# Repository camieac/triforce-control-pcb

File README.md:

# triforce-control-pcb

## Repository Navigation
This repository hosts the electronics hardware designs for the Triforce Fight Controller. Links to the main software repositories are below:

### [Triforce Control](https://github.com/TeamTriforceUK/triforce-control)

The Triforce Control firmware (mbed OS) runs on an LPC1768 (ARM Cortex M3). The firmware is responsible for controlling the robot.

### [Triforce Telemetry](https://github.com/TeamTriforceUK/triforce-telemetry)

The Triforce Telemetry repository hosts firmware (FreeRTOS) for the ESP8266 WiFi chip. This microcontroller works alongside the mbed to provide telemetry functionality via an HTTP server.

The ESP8266 allows us to communicate telemetry from Triforce to connected mobile devices (tablets, laptops, mobile phones). We also control non-safety critical settings such as LED lights from the mobile device.

## System Overview

### Microprocessors

| Device  | Firmware  | Language |
|---------|-----------|----------|
| [LPC1768](https://developer.mbed.org/platforms/mbed-LPC1768/) | [mbed OS](https://www.mbed.com/en/development/mbed-os/)   | C++      |
| [ESP8266](https://www.adafruit.com/product/2471) | [FreeRTOS](http://www.freertos.org/)  | C        |

### Sensors

| Sensor | Purpose                              | Communication |
|--------|--------------------------------------|---------------|
| [BNO055](https://learn.adafruit.com/adafruit-bno055-absolute-orientation-sensor/overview) | Orientation, direction, acceleration |  I2C          |

# PCB Spec

# Board Dimensions

| Width | Height | Thickness |
|-------|--------|-----------|
| 75mm  | 85mm   | 1.6mm     |

# Useful Links

## Enclosure

https://www.hammfg.com/files/parts/pdf/1455J1202.pdf
https://www.hammfg.com/part/1455J1202

## Generating gerber files

http://support.seeedstudio.com/knowledgebase/articles/1824574-how-to-generate-gerber-and-drill-files-from-kicad

## Contributing

We are open to any contributions in terms of ideas, suggestions, bug reports, development. Feel free to open GitHub issues regarding any contributions.

## Licensing

Licensed under CERN OHL v.1.2.

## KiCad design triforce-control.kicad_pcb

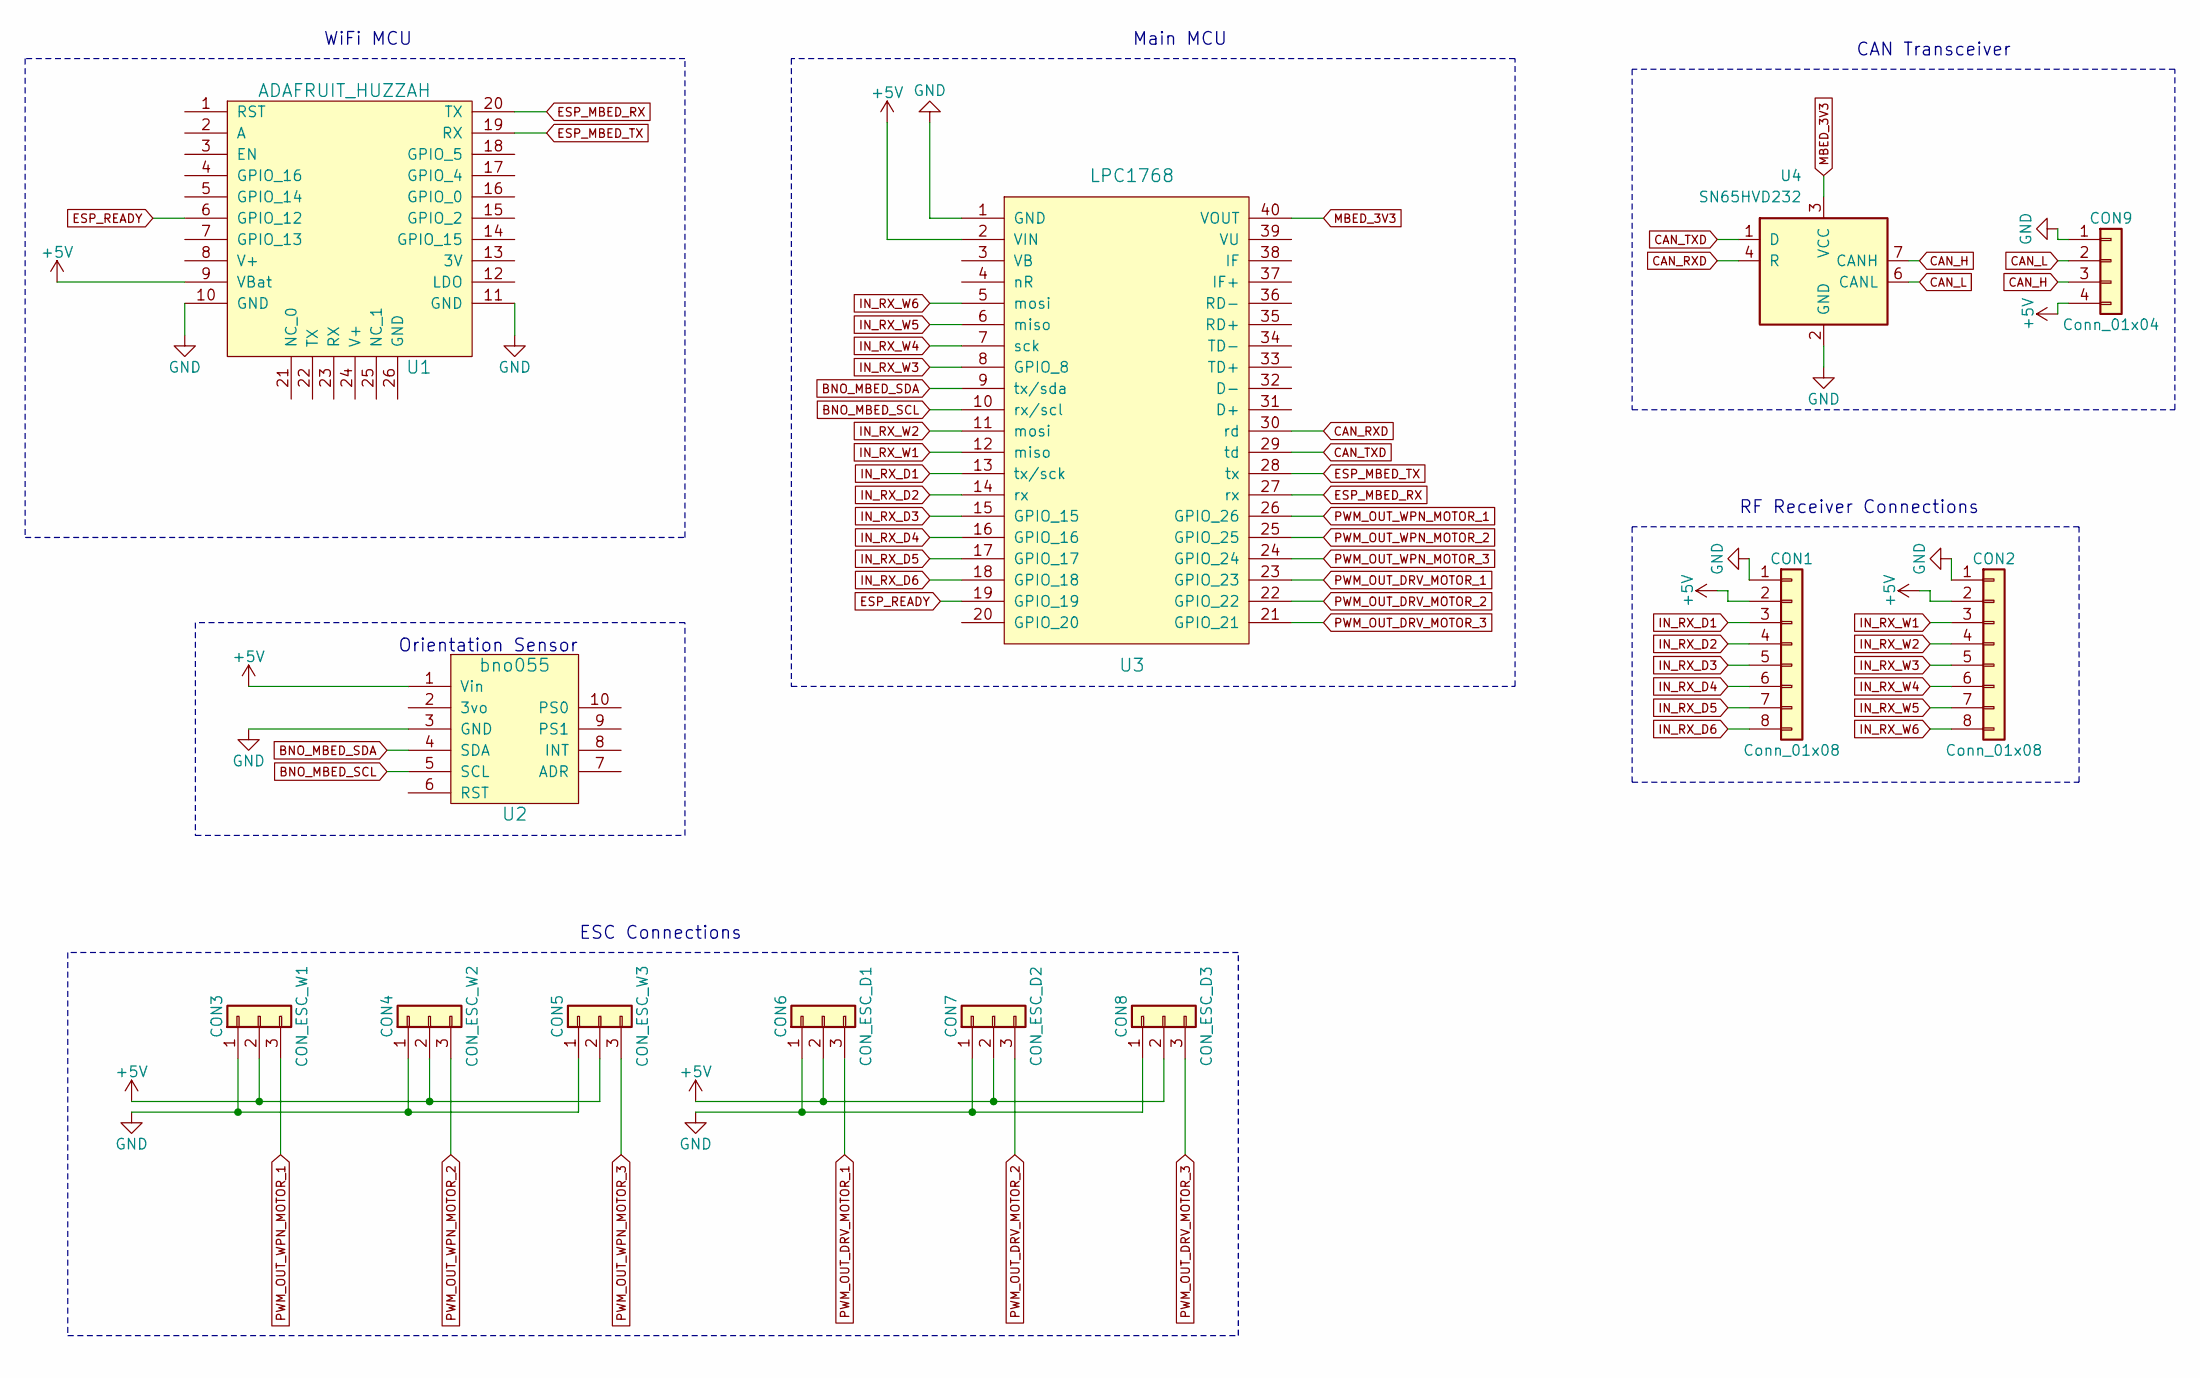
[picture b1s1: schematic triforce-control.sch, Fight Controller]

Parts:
CON1, CON2: Conn_01x08; JST_SH_SM08B-SRSS-TB_08x1.00mm_Angled
CON3: CON_ESC_W1; Pin_Header_Angled_3x01_Pitch2.54mm
CON4: CON_ESC_W2; Pin_Header_Angled_3x01_Pitch2.54mm
CON5: CON_ESC_W3; Pin_Header_Angled_3x01_Pitch2.54mm
CON6: CON_ESC_D1; Pin_Header_Angled_3x01_Pitch2.54mm
CON7: CON_ESC_D2; Pin_Header_Angled_3x01_Pitch2.54mm
CON8: CON_ESC_D3; Pin_Header_Angled_3x01_Pitch2.54mm
CON9: Conn_01x04; JST_PH_S4B-PH-K_04x2.00mm_Angled
U1: ADAFRUIT_HUZZAH; ESP8266
U2: bno055; BNO055
U3: LPC1768; lpc1768
U4: SN65HVD232; SOIC-8_3.9x4.9mm_Pitch1.27mm

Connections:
+5V: CON1.2, CON2.2, CON3.2, CON4.2, CON5.2, CON6.2, CON7.2, CON8.2, CON9.4, U1.9 (VBat), U2.1 (Vin), U3.2 (VIN); also elsewhere on the board
BNO_MBED_SCL: U2.5 (SCL), U3.10 (rx/scl); also elsewhere on the board
BNO_MBED_SDA: U2.4 (SDA), U3.9 (tx/sda); also elsewhere on the board
CAN_H: CON9.3, U4.7 (CANH)
CAN_L: CON9.2, U4.6 (CANL)
CAN_RXD: U3.30 (rd), U4.4 (R); also elsewhere on the board
CAN_TXD: U3.29 (td), U4.1 (D); also elsewhere on the board
ESP_MBED_RX: U1.20 (TX), U3.27 (rx); also elsewhere on the board
ESP_MBED_TX: U1.19 (RX), U3.28 (tx); also elsewhere on the board
ESP_READY: U1.6 (GPIO_12), U3.19 (GPIO_19); also elsewhere on the board
GND: CON1.1, CON2.1, CON3.1, CON4.1, CON5.1, CON6.1, CON7.1, CON8.1, CON9.1, U1.10 (GND), U1.11 (GND), U2.3 (GND), U3.1 (GND), U4.2 (GND); also elsewhere on the board
IN_RX_D1: CON1.3, U3.13 (tx/sck); also elsewhere on the board
IN_RX_D2: CON1.4, U3.14 (rx); also elsewhere on the board
IN_RX_D3: CON1.5, U3.15 (GPIO_15); also elsewhere on the board
IN_RX_D4: CON1.6, U3.16 (GPIO_16); also elsewhere on the board
IN_RX_D5: CON1.7, U3.17 (GPIO_17); also elsewhere on the board
IN_RX_D6: CON1.8, U3.18 (GPIO_18); also elsewhere on the board
IN_RX_W1: CON2.3, U3.12 (miso); also elsewhere on the board
IN_RX_W2: CON2.4, U3.11 (mosi); also elsewhere on the board
IN_RX_W3: CON2.5, U3.8 (GPIO_8); also elsewhere on the board
IN_RX_W4: CON2.6, U3.7 (sck); also elsewhere on the board
IN_RX_W5: CON2.7, U3.6 (miso); also elsewhere on the board
IN_RX_W6: CON2.8, U3.5 (mosi); also elsewhere on the board
MBED_3V3: U3.40 (VOUT), U4.3 (VCC); also elsewhere on the board
unnamed 50: U3.3 (VB); also elsewhere on the board
unnamed 51: U3.4 (nR); also elsewhere on the board
unnamed 52: U3.20 (GPIO_20); also elsewhere on the board
unnamed 53: U3.31 (D+); also elsewhere on the board
unnamed 54: U3.32 (D-); also elsewhere on the board
unnamed 55: U3.33 (TD+); also elsewhere on the board
unnamed 56: U3.34 (TD-); also elsewhere on the board
unnamed 57: U3.35 (RD+); also elsewhere on the board
unnamed 58: U3.36 (RD-); also elsewhere on the board
unnamed 59: U3.37 (IF+); also elsewhere on the board
unnamed 60: U3.38 (IF); also elsewhere on the board
unnamed 61: U3.39 (VU); also elsewhere on the board
PWM_OUT_DRV_MOTOR_1: CON6.3, U3.23 (GPIO_23); also elsewhere on the board
PWM_OUT_DRV_MOTOR_2: CON7.3, U3.22 (GPIO_22); also elsewhere on the board
PWM_OUT_DRV_MOTOR_3: CON8.3, U3.21 (GPIO_21); also elsewhere on the board
PWM_OUT_WPN_MOTOR_1: CON3.3, U3.26 (GPIO_26); also elsewhere on the board
PWM_OUT_WPN_MOTOR_2: CON4.3, U3.25 (GPIO_25); also elsewhere on the board
PWM_OUT_WPN_MOTOR_3: CON5.3, U3.24 (GPIO_24); also elsewhere on the board

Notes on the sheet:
CAN Transceiver
RF Receiver Connections
Orientation Sensor
WiFi MCU
Main MCU
ESC Connections

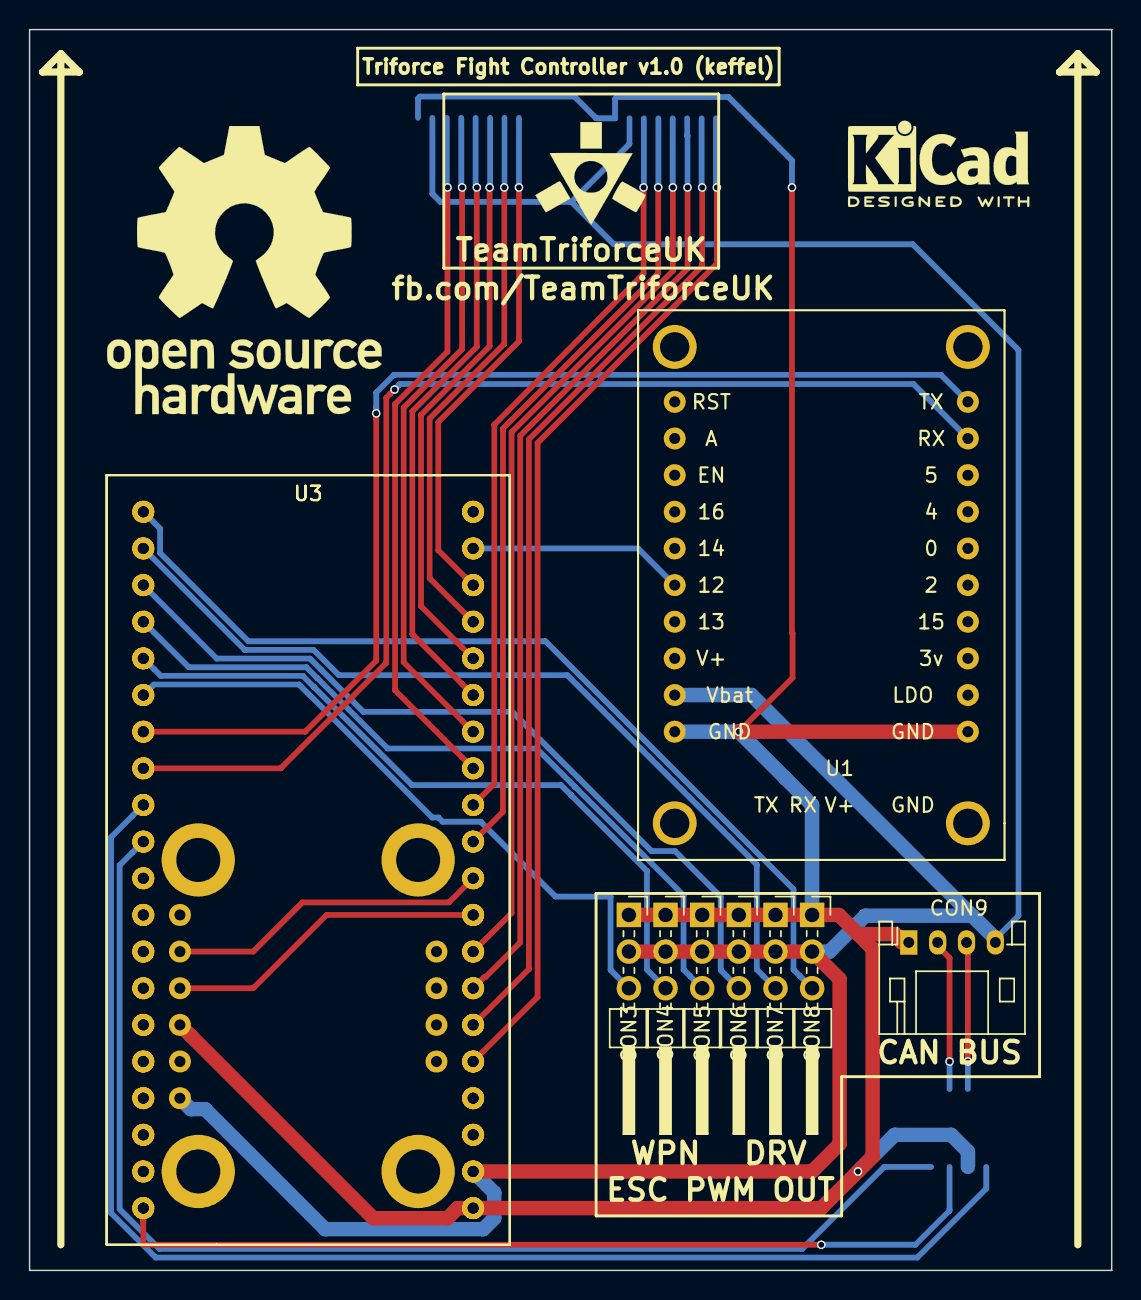
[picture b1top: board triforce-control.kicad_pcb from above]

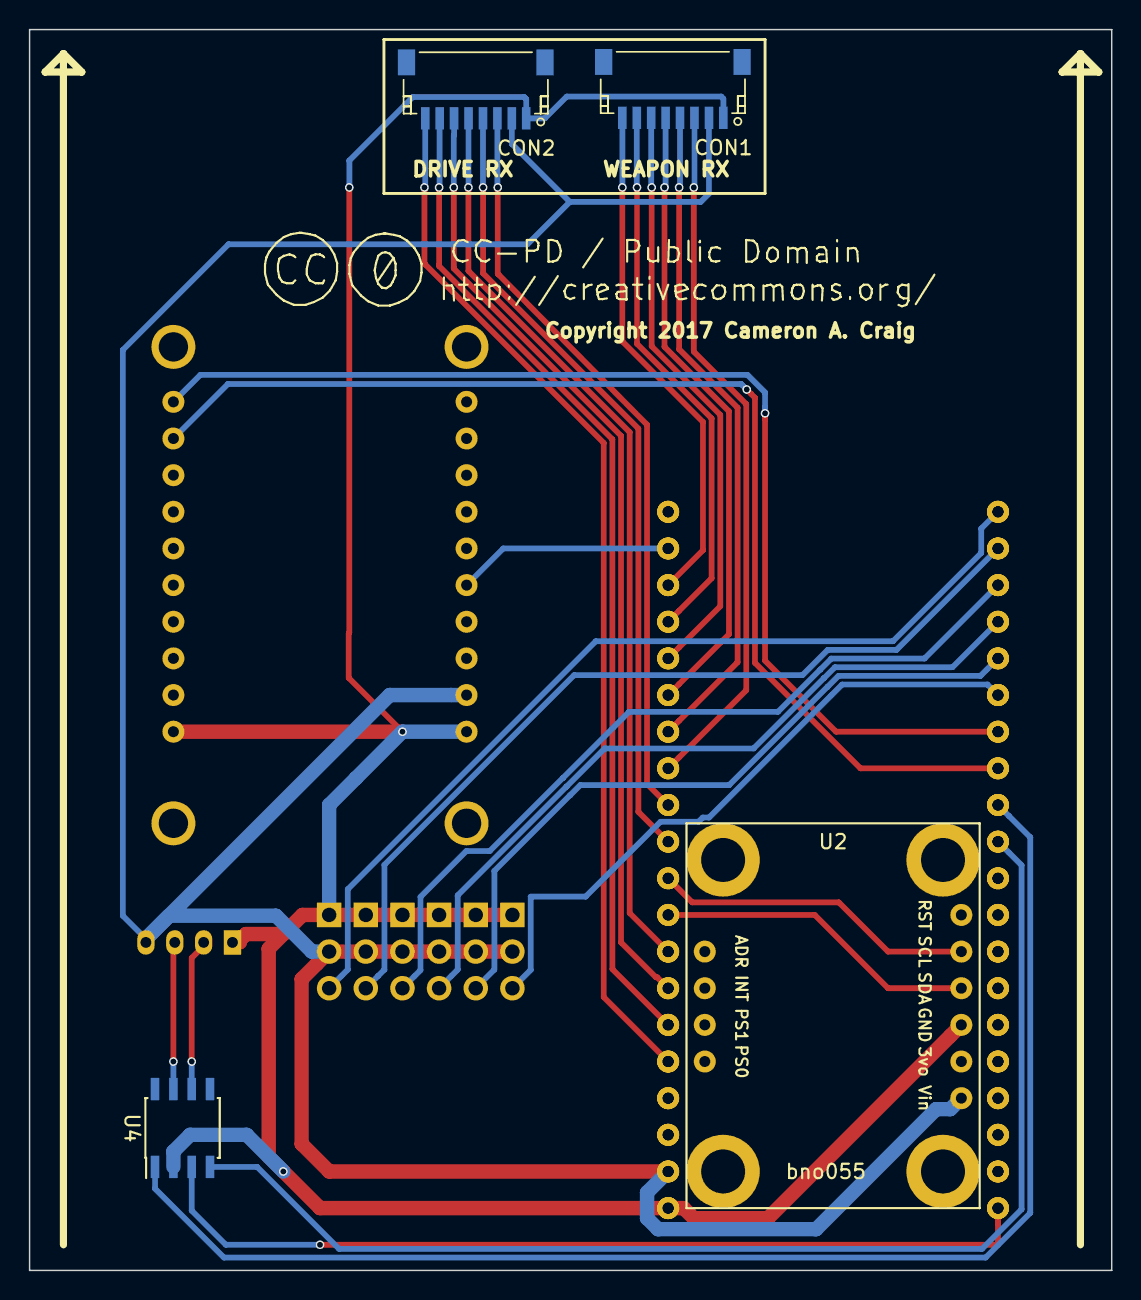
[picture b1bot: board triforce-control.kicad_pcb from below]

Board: 2 copper layers, 75.0 x 86.0 mm, 14 parts (4 on the bottom side), 42 nets.

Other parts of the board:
U3#2: LPC1768; lpc1768

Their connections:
+5V: U3#2.2; also elsewhere on the board
BNO_MBED_SCL: U3#2.10; also elsewhere on the board
BNO_MBED_SDA: U3#2.9; also elsewhere on the board
CAN_RXD: U3#2.30; also elsewhere on the board
CAN_TXD: U3#2.29; also elsewhere on the board
ESP_MBED_RX: U3#2.27; also elsewhere on the board
ESP_MBED_TX: U3#2.28; also elsewhere on the board
ESP_READY: U3#2.19; also elsewhere on the board
GND: U3#2.1; also elsewhere on the board
IN_RX_D1: U3#2.13; also elsewhere on the board
IN_RX_D2: U3#2.14; also elsewhere on the board
IN_RX_D3: U3#2.15; also elsewhere on the board
IN_RX_D4: U3#2.16; also elsewhere on the board
IN_RX_D5: U3#2.17; also elsewhere on the board
IN_RX_D6: U3#2.18; also elsewhere on the board
IN_RX_W1: U3#2.12; also elsewhere on the board
IN_RX_W2: U3#2.11; also elsewhere on the board
IN_RX_W3: U3#2.8; also elsewhere on the board
IN_RX_W4: U3#2.7; also elsewhere on the board
IN_RX_W5: U3#2.6; also elsewhere on the board
IN_RX_W6: U3#2.5; also elsewhere on the board
MBED_3V3: U3#2.40; also elsewhere on the board
unnamed 50: U3#2.3; also elsewhere on the board
unnamed 51: U3#2.4; also elsewhere on the board
unnamed 52: U3#2.20; also elsewhere on the board
unnamed 53: U3#2.31; also elsewhere on the board
unnamed 54: U3#2.32; also elsewhere on the board
unnamed 55: U3#2.33; also elsewhere on the board
unnamed 56: U3#2.34; also elsewhere on the board
unnamed 57: U3#2.35; also elsewhere on the board
unnamed 58: U3#2.36; also elsewhere on the board
unnamed 59: U3#2.37; also elsewhere on the board
unnamed 60: U3#2.38; also elsewhere on the board
unnamed 61: U3#2.39; also elsewhere on the board
PWM_OUT_DRV_MOTOR_1: U3#2.23; also elsewhere on the board
PWM_OUT_DRV_MOTOR_2: U3#2.22; also elsewhere on the board
PWM_OUT_DRV_MOTOR_3: U3#2.21; also elsewhere on the board
PWM_OUT_WPN_MOTOR_1: U3#2.26; also elsewhere on the board
PWM_OUT_WPN_MOTOR_2: U3#2.25; also elsewhere on the board
PWM_OUT_WPN_MOTOR_3: U3#2.24; also elsewhere on the board

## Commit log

2017-12-20 Started new PCB design.
2017-12-21 Added JST and enclosure datasheets.
2017-12-21 Added missing GND connection.
2017-12-23 Prettifying the front silkscreen with symbols and text.
2017-12-23 Started README.md.
2018-01-13 Changed tracks.
2018-01-14 Swapped JSP PH for JST SH on RX inputs.
2018-01-16 Added JST SH 3D model.
2018-01-17 Added Triforce logo and JST SH models.
2018-01-17 Added outline as DXF.
2018-01-17 Moved some tracks.
2018-01-19 Connected an extra ESP8266 ground pin.
2018-01-19 Updated netlist with new ground connection.
2018-01-19 Added silkscreen art.
2018-01-19 Added boundary boxes on silkscreen for connector blocks.
2018-01-19 PCB track cleanup and alignment.
2018-01-19 Added JST SH wrl file.
2018-01-22 Added LICENSE.txt.
2018-01-22 Added CHANGES.txt.
2018-01-22 Added PRODUCT.md
2018-01-23 Moved PCB to pcb folder.
2018-01-23 Started moving component source files to external repository.
2018-01-23 Moved schematics to schematics folder.
2018-01-23 Added folder for manufacturing files.
2018-01-23 Added CERN open hardware license howto guide.
2018-01-23 Removed old lib directory.
2018-01-23 Added board outline drawing.
2018-01-23 Updated project file.
2018-01-23 Added component library.
2018-01-23 Started adding enclosure parts as footprints.
2018-01-25 Added enclosure 3d shapes to PCB.
2018-01-25 Removed unused file.
2018-01-25 Moved netlist to netlist folder.
2018-01-25 Removed old schematic.
2018-01-25 Removed old PCB file.
2018-01-25 Removed old XML file.
2018-01-25 Updated schematics to use components lib.
2018-01-25 Added .gitignore.
2018-01-25 Copied over README info from software repos.
2018-01-25 Removed unused files.
2018-03-23 Started v2.x work, integrating developement boards into PCB.

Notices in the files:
triforce-control.kicad_pcb:
Copyright 2017 Cameron A. Craig
triforce-control.sch:
Copyright Cameron A. Craig 2017
